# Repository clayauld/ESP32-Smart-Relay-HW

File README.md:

# ESP32-Smart-Relay-HW
Smart Relay based on ESP32 microcontroller for use with Home Assistant (home-assistant.io)

---

#### LICENSE Notice

Copyright Clayton Auld 2021.

This source describes Open Hardware and is licensed under the CERN-OHLW v2 or later

You may redistribute and modify this documentation and make products using it under the terms of the CERN-OHL-W v2 (https:/cern.ch/cern-ohl). This documentation is distributed WITHOUT ANY EXPRESS OR IMPLIED WARRANTY, INCLUDING OF MERCHANTABILITY, SATISFACTORY QUALITY AND FITNESS FOR A PARTICULAR PURPOSE. Please see the CERN-OHL-W v2 for applicable conditions.

Source location: https://github.com/clayauld/ESP32-Smart-Relay-HW

As per CERN-OHL-W v2 section 4.1, should You produce hardware based on these sources, You must maintain the Source Location visible on the external case of the White Rabbit switch or other product you make using this documentation.

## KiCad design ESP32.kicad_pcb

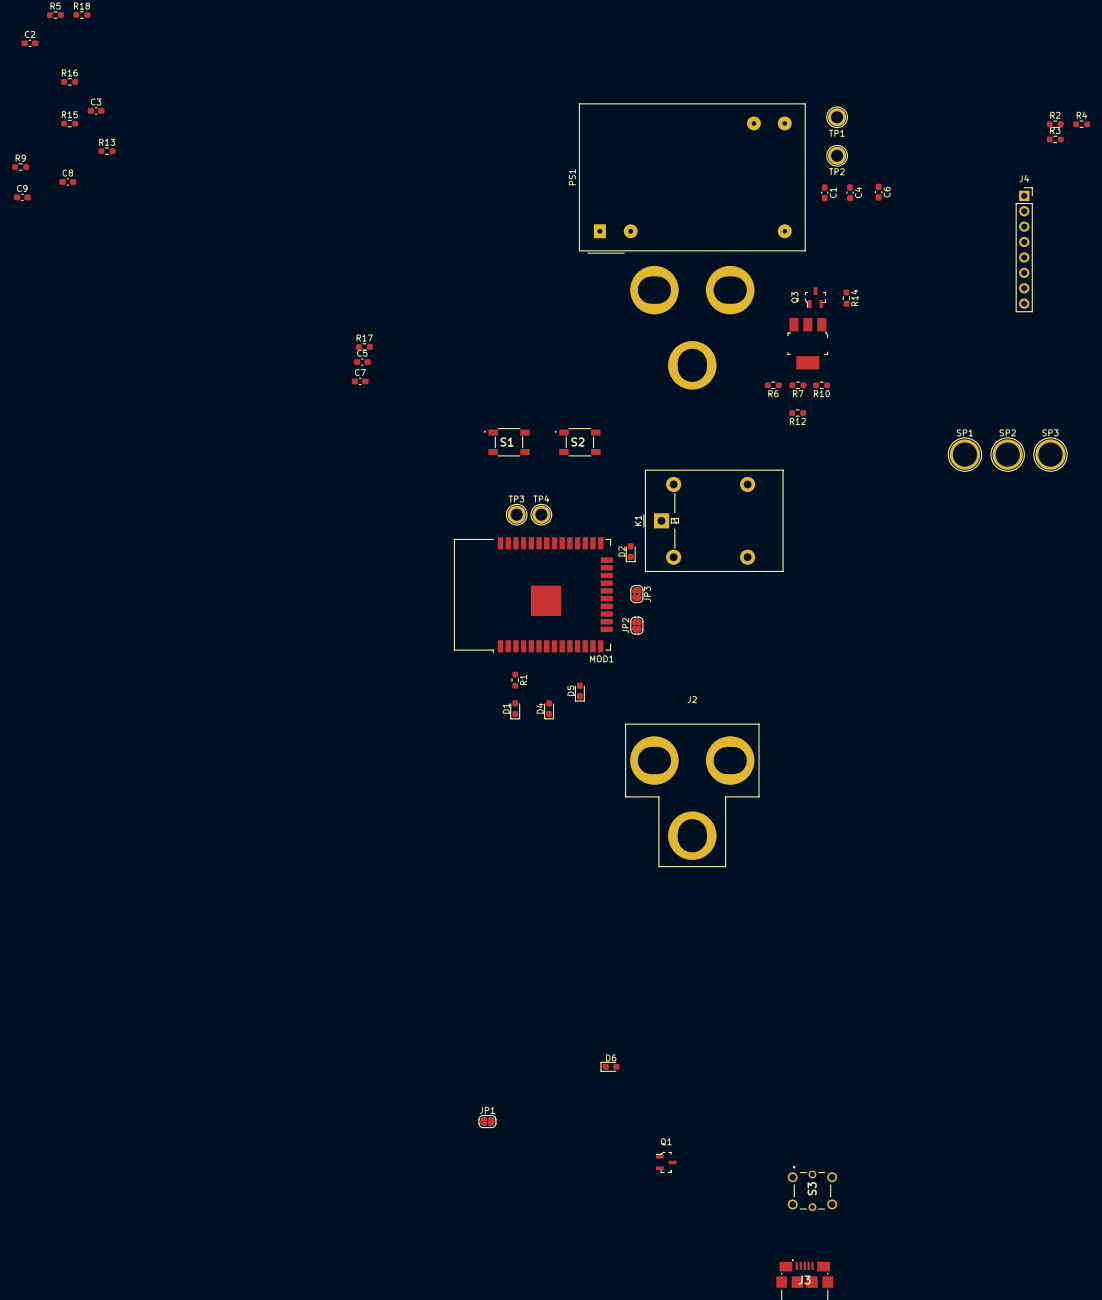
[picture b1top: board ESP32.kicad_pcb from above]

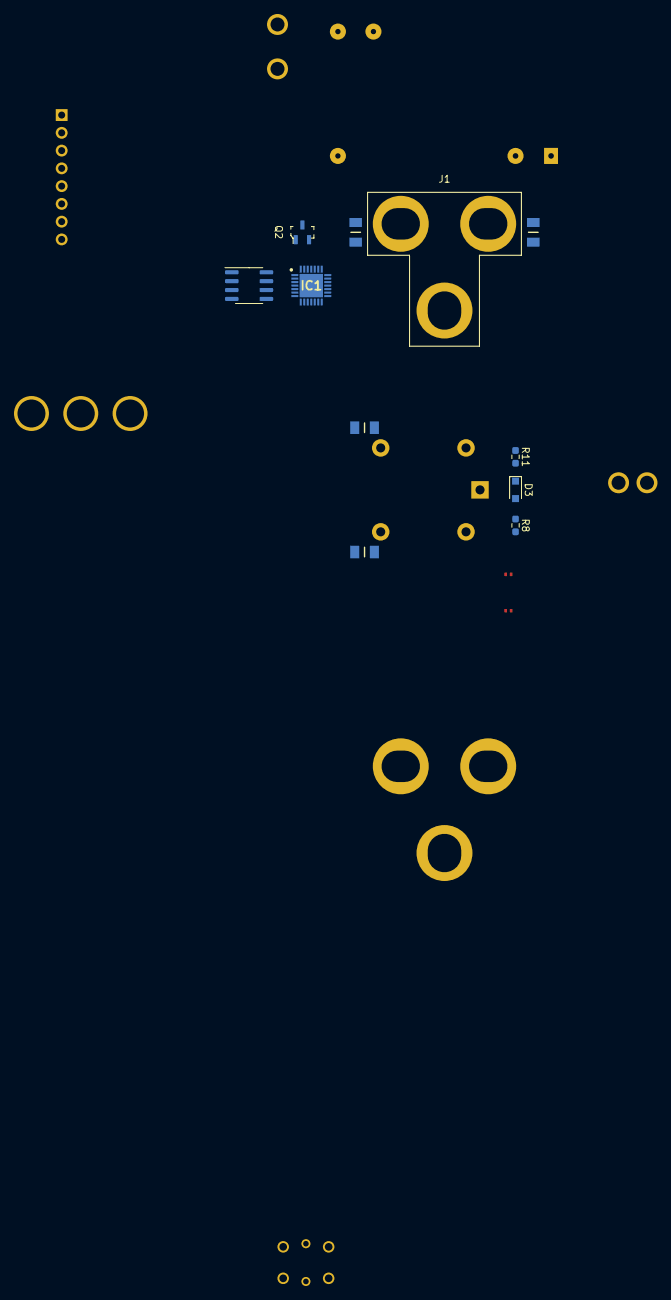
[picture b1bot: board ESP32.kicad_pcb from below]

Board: 4 copper layers, 63 parts (11 on the bottom side), 48 nets, no tracks yet.

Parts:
C1: 22uF; C_0603_1608Metric_Pad1.08x0.95mm_HandSolder
C2, C5, C6, C7, C8, C9: 0.1uF; C_0603_1608Metric_Pad1.08x0.95mm_HandSolder
C3, C4: 4.7uF; C_0603_1608Metric_Pad1.08x0.95mm_HandSolder
D1, D2, D6: RED; LED_0603_1608Metric_Pad1.05x0.95mm_HandSolder
D3: 1N47xxA; D_SOD-323_HandSoldering
D4: GREEN; LED_0603_1608Metric_Pad1.05x0.95mm_HandSolder
D5: BLUE; LED_0603_1608Metric_Pad1.05x0.95mm_HandSolder
F1, F2, F3, F4: C1H10; FUSC3216X85N
IC1: CP2102N-A02-GQFN28R; QFN50P500X500X80-29N-D
J1: NEMA-5-15P-Male
J2: NEMA-5-15R-Female
J3: 10118192-0002LF; 101181920002LF
J4: 0.1" (2.54mm) Headers; PinSocket_1x08_P2.54mm_Vertical
JP1: BJT_Bypass; SolderJumper-2_P1.3mm_Open_RoundedPad1.0x1.5mm
JP2: UART-TX; SolderJumper-2_P1.3mm_Bridged2Bar_RoundedPad1.0x1.5mm
JP3: UART-RX; SolderJumper-2_P1.3mm_Bridged2Bar_RoundedPad1.0x1.5mm
K1: G5LE-1; Relay_SPDT_Omron-G5LE-1
MOD1: ESP32-WROOM-32
PS1: IRM-03-3.3; Converter_ACDC_MeanWell_IRM-03-xx_THT
Q1, Q2, Q3: SS8050; SOT-23-3
R1, R8, R13, R16, R17, R18: 200; R_0603_1608Metric_Pad0.98x0.95mm_HandSolder
R2, R3, R4: 1k; R_0603_1608Metric_Pad0.98x0.95mm_HandSolder
R5, R9, R12, R14, R15: 10k; R_0603_1608Metric_Pad0.98x0.95mm_HandSolder
R6: 22.1k; R_0603_1608Metric_Pad0.98x0.95mm_HandSolder
R7: 47.5k; R_0603_1608Metric_Pad0.98x0.95mm_HandSolder
R10: 2k; R_0603_1608Metric_Pad0.98x0.95mm_HandSolder
R11: 10; R_0603_1608Metric_Pad0.98x0.95mm_HandSolder
S1, S2: PTS647SK38SMTR2LFS
S3: TL1240GQ1JCLR; TL1240YQ1JCLR
SP1, SP2, SP3: SolderPoint; TestPoint_Plated_Hole_D4.0mm
TP1, TP2, TP3, TP4: TestPoint; TestPoint_Plated_Hole_D2.0mm
U1: AP2114H-3_3TRG1; SOT-223
U2: USB6B1; SOIC-8_3.9x4.9mm_P1.27mm

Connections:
+3.3V: J4.3, PS1.16, R1.1, R10.2, U1.2, U1.4
+3V3: C1.1, C2.1, C4.1, C6.1, D2.2, IC1.6, IC1.7, MOD1.2, R2.2, R3.2, R4.2, R5.1, R11.1, R13.1, R16.1, R17.1, TP1.1
AC_GND: J1.3, J2.3
D+: IC1.4, U2.6
D-: IC1.5, U2.7
DTR: IC1.28, Q3.2, R14.2
EN: C5.1, C8.1, MOD1.3, Q2.3, R5.2, S2.3, S2.4
GND: C1.2, C2.2, C3.2, C4.2, C5.2, C6.2, C7.2, C8.2, C9.2, D1.1, D6.1, IC1.3, IC1.29, J3.5, J3.MP1, J3.MP2, J3.MP3, J3.MP4, J3.MP5, J3.MP6, J4.4, MOD1.1, MOD1.15, MOD1.38, MOD1.39, PS1.14, Q1.2, R7.2, R12.2, S1.1, S1.2, S2.1, S2.2, S3.1, S3.2, S3.-, TP2.1, U1.1, U2.4, U2.5
I2C_SCL: J4.1, MOD1.36, R4.1
I2C_SDA: J4.2, MOD1.33, R3.1
IO0: C7.1, MOD1.25, Q3.3, S1.3, S1.4
IO2: C9.1, MOD1.24, S3.3, S3.4
IO4: MOD1.26, R18.1
LINE: F1.1, J1.1
LINE_F: F1.2, K1.1, PS1.1
LINE_OUT: F3.1, F4.2, J2.1, SP1.1
NC: F3.2, K1.4, SP2.1
NEUT: F2.1, J1.2
NEUT_F: F2.2, J2.2, PS1.3
NO: F4.1, K1.3, SP3.1
unnamed: D1.2, R1.2
unnamed: D2.1, R8.2
unnamed: D3.1, K1.5, R11.2
unnamed: D3.2, JP1.1, K1.2, Q1.3, R8.1
unnamed: D4.1, IC1.19
unnamed: D4.2, R13.2
unnamed: D5.1, IC1.18
unnamed: D5.2, R16.2
unnamed: D6.2, R17.2
unnamed: IC1.8, R6.1, R7.1
unnamed: IC1.9, R10.1
unnamed: IC1.11, R12.1
unnamed: J3.2, U2.2
unnamed: J3.3, U2.3
unnamed: JP1.2, Q1.1, R9.1
unnamed: Q2.1, R14.1
unnamed: Q3.1, R15.1
unnamed: R18.2, S3.+
RTS: IC1.24, Q2.2, R15.2
RXD: IC1.25, JP3.1
RXD0: JP3.2, MOD1.34, TP4.1
SPI_MISO: J4.6, MOD1.31
SPI_MOSI: J4.7, MOD1.37
SPI_SCLK: J4.5, MOD1.30
SPI_SS: J4.8, MOD1.29, R2.1
TXD: IC1.26, JP2.1
TXD0: JP2.2, MOD1.35, TP3.1
VBUS: C3.1, J3.1, R6.2, U1.3, U2.1, U2.8

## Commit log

2021-01-01 Added existing KiCAD files and PDF
2021-01-13 Added solder points for connecting relay outputs to NEMA female Line_Out
2021-03-03 Added License - CERN Open Hardware Licence Version 2 - Weakly Reciprocal
